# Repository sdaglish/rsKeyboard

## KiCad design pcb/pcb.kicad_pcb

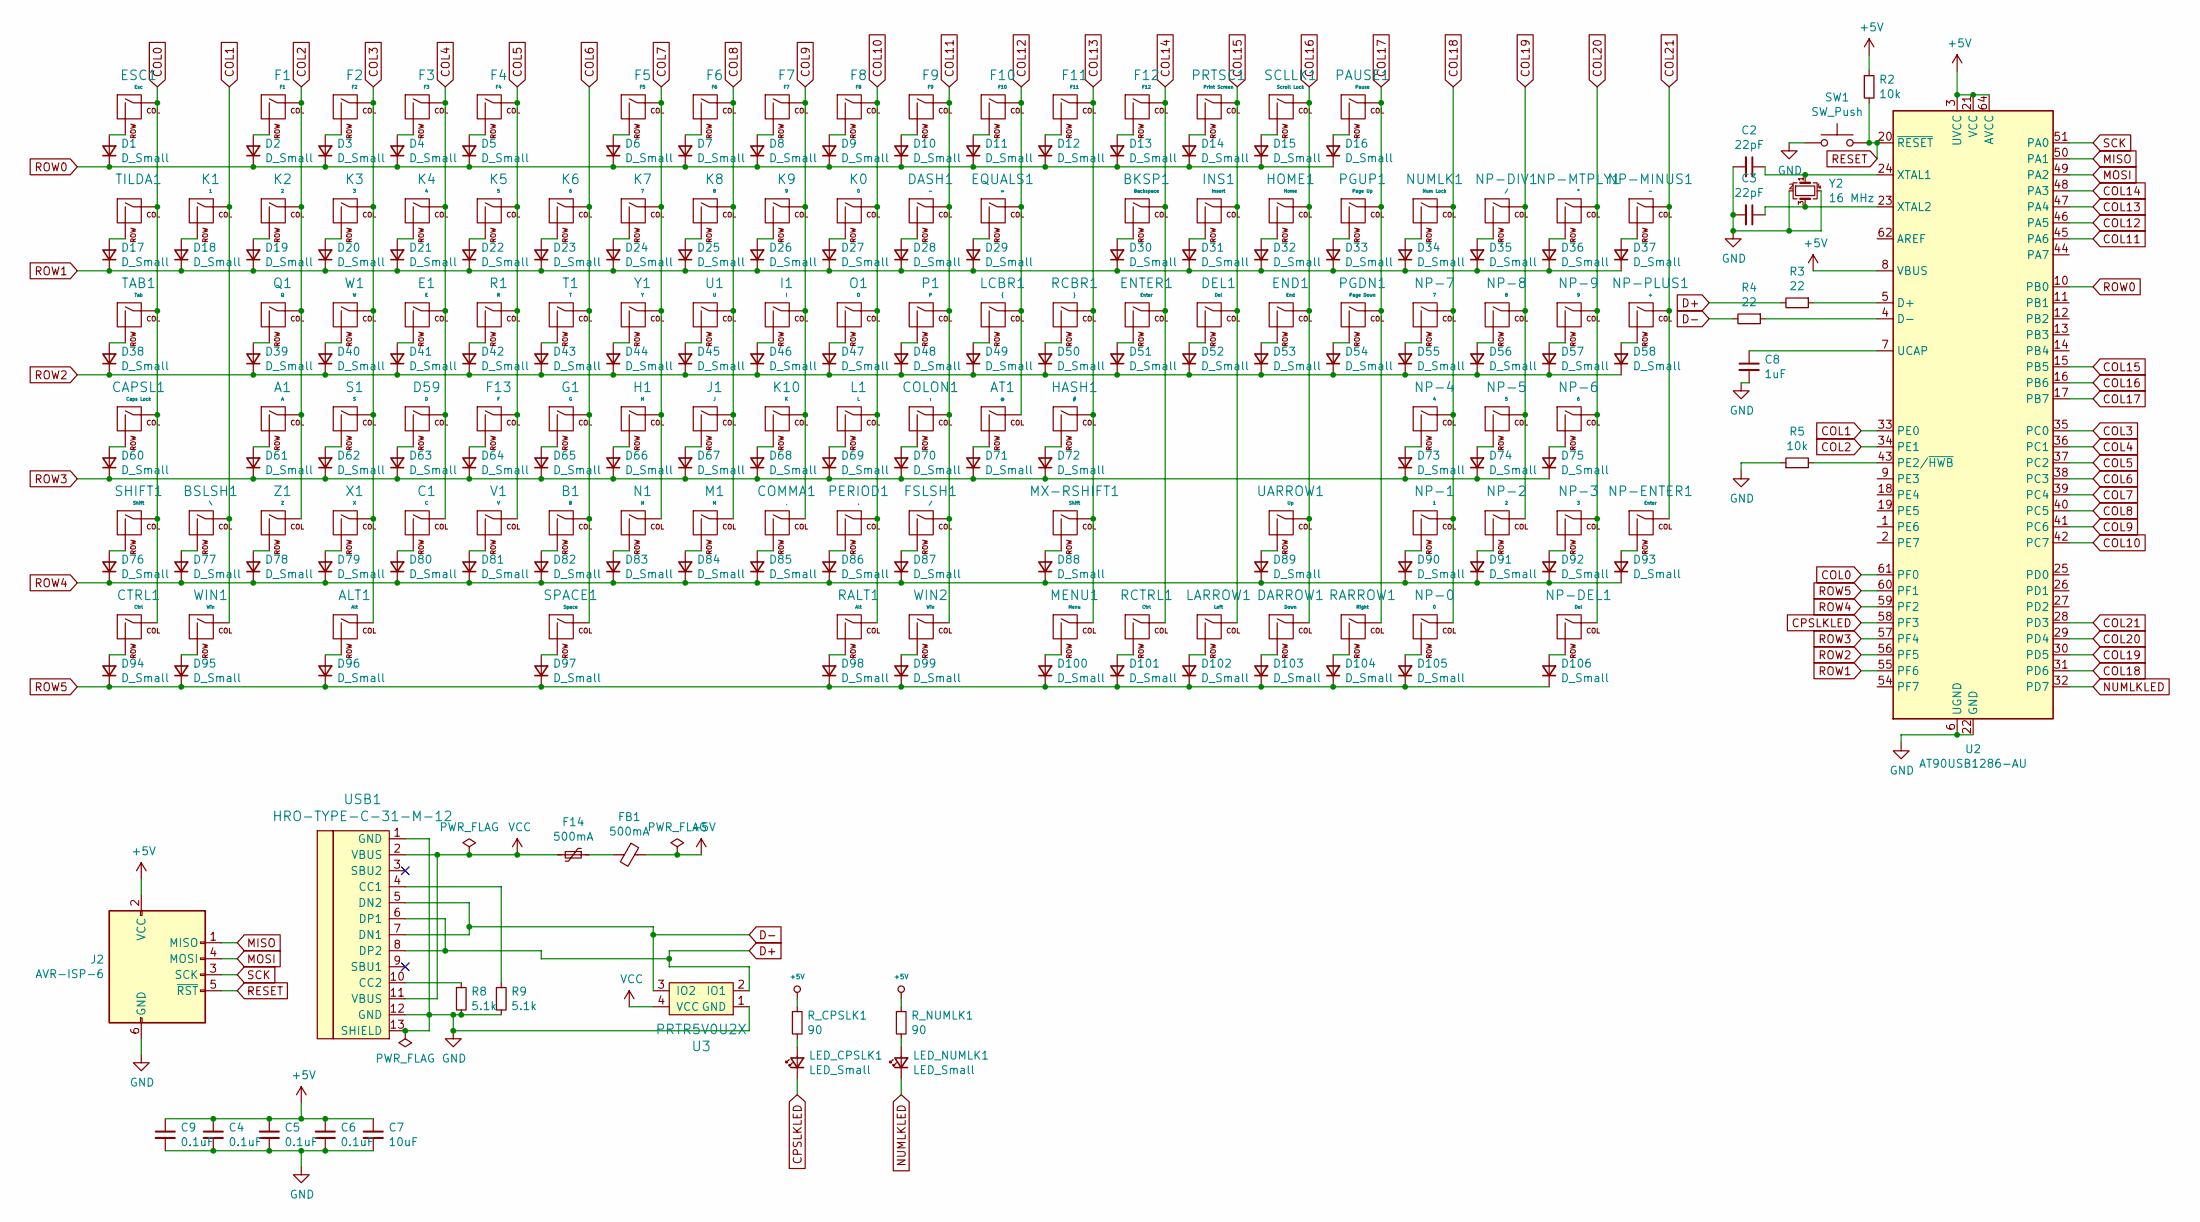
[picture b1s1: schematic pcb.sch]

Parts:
A1: A; MX-1U-NoLED
ALT1: Alt; MX-1U-NoLED
AT1: @; MX-1U-NoLED
B1: B; MX-1U-NoLED
BKSP1: Backspace; MX-2U-NoLED
BSLSH1: \\; MX-1U-NoLED
C1: C; MX-1U-NoLED
C2, C3: 22pF; C_0805_2012Metric
C4, C5, C6, C9: 0.1uF; C_0805_2012Metric
C7: 10uF; C_0805_2012Metric
C8: 1uF; C_0805_2012Metric
CAPSL1: Caps Lock; MX-1U-NoLED
COLON1: :; MX-1U-NoLED
COMMA1: ,; MX-1U-NoLED
CTRL1: Ctrl; MX-1U-NoLED
D1, D2, D3, D4, D5, D6, D7, D8, D9, D10, D11, D12, D13, D14, D15, D16, D17, D18, D19, D20, D21, D22, D23, D24, D25, D26, D27, D28, D29, D30, D31, D32, D33, D34, D35, D36, D37, D38, D39, D40, D41, D42, D43, D44, D45, D46, D47, D48, D49, D50, D51, D52, D53, D54, D55, D56, D57, D58, D60, D61, D62, D63, D64, D65, D66, D67, D68, D69, D70, D71, D72, D73, D74, D75, D76, D77, D78, D79, D80, D81, D82, D83, D84, D85, D86, D87, D88, D89, D90, D91, D92, D93, D94, D95, D96, D97, D98, D99, D100, D101, D102, D103, D104, D105, D106: D_Small; D_SOD-123
D59: D; MX-1U-NoLED
DARROW1: Down; MX-1U-NoLED
DASH1: -; MX-1U-NoLED
DEL1: Del; MX-1U-NoLED
E1: E; MX-1U-NoLED
END1: End; MX-1U-NoLED
ENTER1: Enter; MX-2U-NoLED
EQUALS1: =; MX-1U-NoLED
ESC1: Esc; MX-1U-NoLED
F1: F1; MX-1U-NoLED
F2: F2; MX-1U-NoLED
F3: F3; MX-1U-NoLED
F4: F4; MX-1U-NoLED
F5: F5; MX-1U-NoLED
F6: F6; MX-1U-NoLED
F7: F7; MX-1U-NoLED
F8: F8; MX-1U-NoLED
F9: F9; MX-1U-NoLED
F10: F10; MX-1U-NoLED
F11: F11; MX-1U-NoLED
F12: F12; MX-1U-NoLED
F13: F; MX-1U-NoLED
F14: 500mA; Fuse_0805_2012Metric
FB1: 500mA; R_0805_2012Metric
FSLSH1: /; MX-1U-NoLED
G1: G; MX-1U-NoLED
H1: H; MX-1U-NoLED
HASH1: #; MX-1U-NoLED
HOME1: Home; MX-1U-NoLED
I1: I; MX-1U-NoLED
INS1: Insert; MX-1U-NoLED
J1: J; MX-1U-NoLED
J2: AVR-ISP-6; Reset_Pretty-Mask
K0: 0; MX-1U-NoLED
K1: 1; MX-1U-NoLED
K2: 2; MX-1U-NoLED
K3: 3; MX-1U-NoLED
K4: 4; MX-1U-NoLED
K5: 5; MX-1U-NoLED
K6: 6; MX-1U-NoLED
K7: 7; MX-1U-NoLED
K8: 8; MX-1U-NoLED
K9: 9; MX-1U-NoLED
K10: K; MX-1U-NoLED
L1: L; MX-1U-NoLED
LARROW1: Left; MX-1U-NoLED
LCBR1: {; MX-1U-NoLED
LED_CPSLK1: LED_Small; LED_0805_2012Metric
LED_NUMLK1: LED_Small; LED_0805_2012Metric
M1: M; MX-1U-NoLED
MENU1: Menu; MX-1U-NoLED
MX-RSHIFT1: Shift; MX-2.75U-NoLED
N1: N; MX-1U-NoLED
NP-0: 0; MX-2U-NoLED
NP-1: 1; MX-1U-NoLED
NP-2: 2; MX-1U-NoLED
NP-3: 3; MX-1U-NoLED
NP-4: 4; MX-1U-NoLED
NP-5: 5; MX-1U-NoLED
NP-6: 6; MX-1U-NoLED
NP-7: 7; MX-1U-NoLED
NP-8: 8; MX-1U-NoLED
NP-9: 9; MX-1U-NoLED
NP-DEL1: Del; MX-1U-NoLED
NP-DIV1: /; MX-1U-NoLED
NP-ENTER1: Enter; MX-2U-NoLED
NP-MINUS1: -; MX-1U-NoLED
NP-MTPLY1: *; MX-1U-NoLED
NP-PLUS1: +; MX-2U-NoLED
NUMLK1: Num Lock; MX-1U-NoLED
O1: O; MX-1U-NoLED
P1: P; MX-1U-NoLED
PAUSE1: Pause; MX-1U-NoLED
PERIOD1: .; MX-1U-NoLED
PGDN1: Page Down; MX-1U-NoLED
PGUP1: Page Up; MX-1U-NoLED
PRTSC1: Print Screen; MX-1U-NoLED
Q1: Q; MX-1U-NoLED
R1: R; MX-1U-NoLED
R2, R5: 10k; R_0805_2012Metric
R3, R4: 22; R_0805_2012Metric
R8, R9: 5.1k; R_0805_2012Metric
RALT1: Alt; MX-1U-NoLED
RARROW1: Right; MX-1U-NoLED
RCBR1: }; MX-1U-NoLED
RCTRL1: Ctrl; MX-1U-NoLED
R_CPSLK1: 90; R_0805_2012Metric
R_NUMLK1: 90; R_0805_2012Metric
S1: S; MX-1U-NoLED
SCLLK1: Scroll Lock; MX-1U-NoLED
SHIFT1: Shift; MX-1U-NoLED
SPACE1: Space; MX-6.25U-NoLED
SW1: SW_Push; SKQG-1155865
T1: T; MX-1U-NoLED
TAB1: Tab; MX-1U-NoLED
TILDA1: MX-1U-NoLED
U1: U; MX-1U-NoLED
U2: AT90USB1286-AU; TQFP-64_14x14mm_P0.8mm
U3: PRTR5V0U2X; SOT143B
UARROW1: Up; MX-1U-NoLED
USB1: HRO-TYPE-C-31-M-12
V1: V; MX-1U-NoLED
W1: W; MX-1U-NoLED
WIN1, WIN2: Win; MX-1U-NoLED
X1: X; MX-1U-NoLED
Y1: Y; MX-1U-NoLED
Y2: 16 MHz; Crystal_SMD_3225-4Pin_3.2x2.5mm
Z1: Z; MX-1U-NoLED

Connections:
+5V: C4.1, C5.1, C6.1, C7.1, C9.1, FB1.1, J2.2 (VCC), R2.1, R_CPSLK1.1, R_NUMLK1.1, U2.3 (UVCC), U2.8 (VBUS), U2.21 (VCC), U2.52 (VCC), U2.64 (AVCC)
COL0: CAPSL1.1 (COL), CTRL1.1 (COL), ESC1.1 (COL), SHIFT1.1 (COL), TAB1.1 (COL), TILDA1.1 (COL), U2.61 (PF0)
COL1: BSLSH1.1 (COL), K1.1 (COL), U2.33 (PE0), WIN1.1 (COL)
COL2: A1.1 (COL), F1.1 (COL), K2.1 (COL), Q1.1 (COL), U2.34 (PE1), Z1.1 (COL)
COL3: ALT1.1 (COL), F2.1 (COL), K3.1 (COL), S1.1 (COL), U2.35 (PC0), W1.1 (COL), X1.1 (COL)
COL4: C1.1 (COL), D59.1 (COL), E1.1 (COL), F3.1 (COL), K4.1 (COL), U2.36 (PC1)
COL5: F4.1 (COL), F13.1 (COL), K5.1 (COL), R1.1 (COL), U2.37 (PC2), V1.1 (COL)
COL6: B1.1 (COL), G1.1 (COL), K6.1 (COL), SPACE1.1 (COL), T1.1 (COL), U2.38 (PC3)
COL7: F5.1 (COL), H1.1 (COL), K7.1 (COL), N1.1 (COL), U2.39 (PC4), Y1.1 (COL)
COL8: F6.1 (COL), J1.1 (COL), K8.1 (COL), M1.1 (COL), U1.1 (COL), U2.40 (PC5)
COL9: COMMA1.1 (COL), F7.1 (COL), I1.1 (COL), K9.1 (COL), K10.1 (COL), U2.41 (PC6)
COL10: F8.1 (COL), K0.1 (COL), L1.1 (COL), O1.1 (COL), PERIOD1.1 (COL), RALT1.1 (COL), U2.42 (PC7)
COL11: COLON1.1 (COL), DASH1.1 (COL), F9.1 (COL), FSLSH1.1 (COL), P1.1 (COL), U2.45 (PA6), WIN2.1 (COL)
COL12: AT1.1 (COL), EQUALS1.1 (COL), F10.1 (COL), LCBR1.1 (COL), U2.46 (PA5)
COL13: F11.1 (COL), HASH1.1 (COL), MENU1.1 (COL), MX-RSHIFT1.1 (COL), RCBR1.1 (COL), U2.47 (PA4)
COL14: BKSP1.1 (COL), ENTER1.1 (COL), F12.1 (COL), RCTRL1.1 (COL), U2.48 (PA3)
COL15: DEL1.1 (COL), INS1.1 (COL), LARROW1.1 (COL), PRTSC1.1 (COL), U2.15 (PB5)
COL16: DARROW1.1 (COL), END1.1 (COL), HOME1.1 (COL), SCLLK1.1 (COL), U2.16 (PB6), UARROW1.1 (COL)
COL17: PAUSE1.1 (COL), PGDN1.1 (COL), PGUP1.1 (COL), RARROW1.1 (COL), U2.17 (PB7)
COL18: NP-0.1 (COL), NP-1.1 (COL), NP-4.1 (COL), NP-7.1 (COL), NUMLK1.1 (COL), U2.31 (PD6)
COL19: NP-2.1 (COL), NP-5.1 (COL), NP-8.1 (COL), NP-DIV1.1 (COL), U2.30 (PD5)
COL20: NP-3.1 (COL), NP-6.1 (COL), NP-9.1 (COL), NP-DEL1.1 (COL), NP-MTPLY1.1 (COL), U2.29 (PD4)
COL21: NP-ENTER1.1 (COL), NP-MINUS1.1 (COL), NP-PLUS1.1 (COL), U2.28 (PD3)
CPSLKLED: LED_CPSLK1.1 (K), U2.58 (PF3)
D+: R3.2, U3.2 (IO1), USB1.6 (DP1), USB1.8 (DP2)
D-: R4.2, U3.3 (IO2), USB1.5 (DN2), USB1.7 (DN1)
GND: C2.2, C3.2, C4.2, C5.2, C6.2, C7.2, C8.2, C9.2, J2.6 (GND), R5.1, R8.2, R9.2, SW1.1, U2.6 (UGND), U2.22 (GND), U2.53 (GND), U2.63 (GND), U3.1 (GND), USB1.1 (GND), USB1.12 (GND), USB1.13 (SHIELD), Y2.2, Y2.4
MISO: J2.1 (MISO), U2.50 (PA1)
MOSI: J2.4 (MOSI), U2.49 (PA2)
NUMLKLED: LED_NUMLK1.1 (K), U2.32 (PD7)
unnamed: A1.2 (ROW), D61.2 (A)
unnamed: ALT1.2 (ROW), D96.2 (A)
unnamed: AT1.2 (ROW), D71.2 (A)
unnamed: B1.2 (ROW), D82.2 (A)
unnamed: BKSP1.2 (ROW), D30.2 (A)
unnamed: BSLSH1.2 (ROW), D77.2 (A)
unnamed: C1.2 (ROW), D80.2 (A)
unnamed: C2.1, U2.24 (XTAL1), Y2.1
unnamed: C3.1, U2.23 (XTAL2), Y2.3
unnamed: C8.1, U2.7 (UCAP)
unnamed: CAPSL1.2 (ROW), D60.2 (A)
unnamed: COLON1.2 (ROW), D70.2 (A)
unnamed: COMMA1.2 (ROW), D85.2 (A)
unnamed: CTRL1.2 (ROW), D94.2 (A)
unnamed: D1.2 (A), ESC1.2 (ROW)
unnamed: D2.2 (A), F1.2 (ROW)
unnamed: D3.2 (A), F2.2 (ROW)
unnamed: D4.2 (A), F3.2 (ROW)
unnamed: D5.2 (A), F4.2 (ROW)
unnamed: D6.2 (A), F5.2 (ROW)
unnamed: D7.2 (A), F6.2 (ROW)
unnamed: D8.2 (A), F7.2 (ROW)
unnamed: D9.2 (A), F8.2 (ROW)
unnamed: D10.2 (A), F9.2 (ROW)
unnamed: D11.2 (A), F10.2 (ROW)
unnamed: D12.2 (A), F11.2 (ROW)
unnamed: D13.2 (A), F12.2 (ROW)
unnamed: D14.2 (A), PRTSC1.2 (ROW)
unnamed: D15.2 (A), SCLLK1.2 (ROW)
unnamed: D16.2 (A), PAUSE1.2 (ROW)
unnamed: D17.2 (A), TILDA1.2 (ROW)
unnamed: D18.2 (A), K1.2 (ROW)
unnamed: D19.2 (A), K2.2 (ROW)
unnamed: D20.2 (A), K3.2 (ROW)
unnamed: D21.2 (A), K4.2 (ROW)
unnamed: D22.2 (A), K5.2 (ROW)
unnamed: D23.2 (A), K6.2 (ROW)
unnamed: D24.2 (A), K7.2 (ROW)
unnamed: D25.2 (A), K8.2 (ROW)
unnamed: D26.2 (A), K9.2 (ROW)
unnamed: D27.2 (A), K0.2 (ROW)
unnamed: D28.2 (A), DASH1.2 (ROW)
unnamed: D29.2 (A), EQUALS1.2 (ROW)
unnamed: D31.2 (A), INS1.2 (ROW)
unnamed: D32.2 (A), HOME1.2 (ROW)
unnamed: D33.2 (A), PGUP1.2 (ROW)
unnamed: D34.2 (A), NUMLK1.2 (ROW)
unnamed: D35.2 (A), NP-DIV1.2 (ROW)
unnamed: D36.2 (A), NP-MTPLY1.2 (ROW)
unnamed: D37.2 (A), NP-MINUS1.2 (ROW)
unnamed: D38.2 (A), TAB1.2 (ROW)
unnamed: D39.2 (A), Q1.2 (ROW)
unnamed: D40.2 (A), W1.2 (ROW)
unnamed: D41.2 (A), E1.2 (ROW)
unnamed: D42.2 (A), R1.2 (ROW)
unnamed: D43.2 (A), T1.2 (ROW)
unnamed: D44.2 (A), Y1.2 (ROW)
unnamed: D45.2 (A), U1.2 (ROW)
unnamed: D46.2 (A), I1.2 (ROW)
unnamed: D47.2 (A), O1.2 (ROW)
unnamed: D48.2 (A), P1.2 (ROW)
unnamed: D49.2 (A), LCBR1.2 (ROW)
unnamed: D50.2 (A), RCBR1.2 (ROW)
unnamed: D51.2 (A), ENTER1.2 (ROW)
unnamed: D52.2 (A), DEL1.2 (ROW)
unnamed: D53.2 (A), END1.2 (ROW)
unnamed: D54.2 (A), PGDN1.2 (ROW)
unnamed: D55.2 (A), NP-7.2 (ROW)
unnamed: D56.2 (A), NP-8.2 (ROW)
unnamed: D57.2 (A), NP-9.2 (ROW)
unnamed: D58.2 (A), NP-PLUS1.2 (ROW)
unnamed: D59.2 (ROW), D63.2 (A)
unnamed: D62.2 (A), S1.2 (ROW)
unnamed: D64.2 (A), F13.2 (ROW)
unnamed: D65.2 (A), G1.2 (ROW)
unnamed: D66.2 (A), H1.2 (ROW)
unnamed: D67.2 (A), J1.2 (ROW)
unnamed: D68.2 (A), K10.2 (ROW)
unnamed: D69.2 (A), L1.2 (ROW)
unnamed: D72.2 (A), HASH1.2 (ROW)
unnamed: D73.2 (A), NP-4.2 (ROW)
unnamed: D74.2 (A), NP-5.2 (ROW)
unnamed: D75.2 (A), NP-6.2 (ROW)
unnamed: D76.2 (A), SHIFT1.2 (ROW)
unnamed: D78.2 (A), Z1.2 (ROW)
unnamed: D79.2 (A), X1.2 (ROW)
unnamed: D81.2 (A), V1.2 (ROW)
unnamed: D83.2 (A), N1.2 (ROW)
unnamed: D84.2 (A), M1.2 (ROW)
unnamed: D86.2 (A), PERIOD1.2 (ROW)
unnamed: D87.2 (A), FSLSH1.2 (ROW)
unnamed: D88.2 (A), MX-RSHIFT1.2 (ROW)
unnamed: D89.2 (A), UARROW1.2 (ROW)
unnamed: D90.2 (A), NP-1.2 (ROW)
unnamed: D91.2 (A), NP-2.2 (ROW)
unnamed: D92.2 (A), NP-3.2 (ROW)
unnamed: D93.2 (A), NP-ENTER1.2 (ROW)
unnamed: D95.2 (A), WIN1.2 (ROW)
unnamed: D97.2 (A), SPACE1.2 (ROW)
unnamed: D98.2 (A), RALT1.2 (ROW)
unnamed: D99.2 (A), WIN2.2 (ROW)
unnamed: D100.2 (A), MENU1.2 (ROW)
unnamed: D101.2 (A), RCTRL1.2 (ROW)
unnamed: D102.2 (A), LARROW1.2 (ROW)
unnamed: D103.2 (A), DARROW1.2 (ROW)
unnamed: D104.2 (A), RARROW1.2 (ROW)
unnamed: D105.2 (A), NP-0.2 (ROW)
unnamed: D106.2 (A), NP-DEL1.2 (ROW)
unnamed: F14.1, FB1.2
unnamed: LED_CPSLK1.2 (A), R_CPSLK1.2
unnamed: LED_NUMLK1.2 (A), R_NUMLK1.2
unnamed: R3.1, U2.5 (D+)
unnamed: R4.1, U2.4 (D-)
unnamed: R5.2, U2.43 (PE2/~HWB)
unnamed: R8.1, USB1.10 (CC2)
unnamed: R9.1, USB1.4 (CC1)
RESET: J2.5 (~RST), R2.2, SW1.2, U2.20 (~RESET)
ROW0: D1.1 (K), D2.1 (K), D3.1 (K), D4.1 (K), D5.1 (K), D6.1 (K), D7.1 (K), D8.1 (K), D9.1 (K), D10.1 (K), D11.1 (K), D12.1 (K), D13.1 (K), D14.1 (K), D15.1 (K), D16.1 (K), U2.10 (PB0)
ROW1: D17.1 (K), D18.1 (K), D19.1 (K), D20.1 (K), D21.1 (K), D22.1 (K), D23.1 (K), D24.1 (K), D25.1 (K), D26.1 (K), D27.1 (K), D28.1 (K), D29.1 (K), D30.1 (K), D31.1 (K), D32.1 (K), D33.1 (K), D34.1 (K), D35.1 (K), D36.1 (K), D37.1 (K), U2.55 (PF6)
ROW2: D38.1 (K), D39.1 (K), D40.1 (K), D41.1 (K), D42.1 (K), D43.1 (K), D44.1 (K), D45.1 (K), D46.1 (K), D47.1 (K), D48.1 (K), D49.1 (K), D50.1 (K), D51.1 (K), D52.1 (K), D53.1 (K), D54.1 (K), D55.1 (K), D56.1 (K), D57.1 (K), D58.1 (K), U2.56 (PF5)
ROW3: D60.1 (K), D61.1 (K), D62.1 (K), D63.1 (K), D64.1 (K), D65.1 (K), D66.1 (K), D67.1 (K), D68.1 (K), D69.1 (K), D70.1 (K), D71.1 (K), D72.1 (K), D73.1 (K), D74.1 (K), D75.1 (K), U2.57 (PF4)
ROW4: D76.1 (K), D77.1 (K), D78.1 (K), D79.1 (K), D80.1 (K), D81.1 (K), D82.1 (K), D83.1 (K), D84.1 (K), D85.1 (K), D86.1 (K), D87.1 (K), D88.1 (K), D89.1 (K), D90.1 (K), D91.1 (K), D92.1 (K), D93.1 (K), U2.59 (PF2)
ROW5: D94.1 (K), D95.1 (K), D96.1 (K), D97.1 (K), D98.1 (K), D99.1 (K), D100.1 (K), D101.1 (K), D102.1 (K), D103.1 (K), D104.1 (K), D105.1 (K), D106.1 (K), U2.60 (PF1)
SCK: J2.3 (SCK), U2.51 (PA0)
VCC: F14.2, U3.4 (VCC), USB1.2 (VBUS), USB1.11 (VBUS)

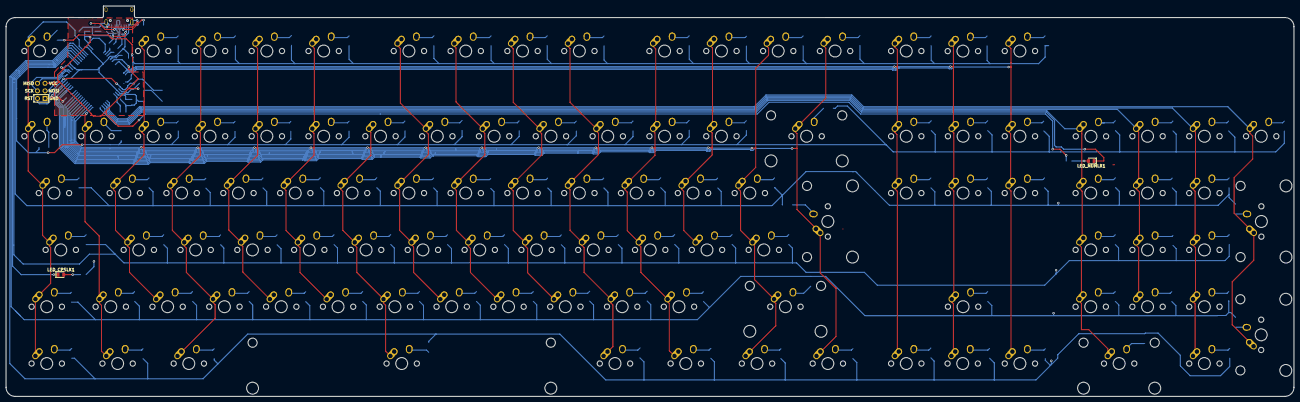
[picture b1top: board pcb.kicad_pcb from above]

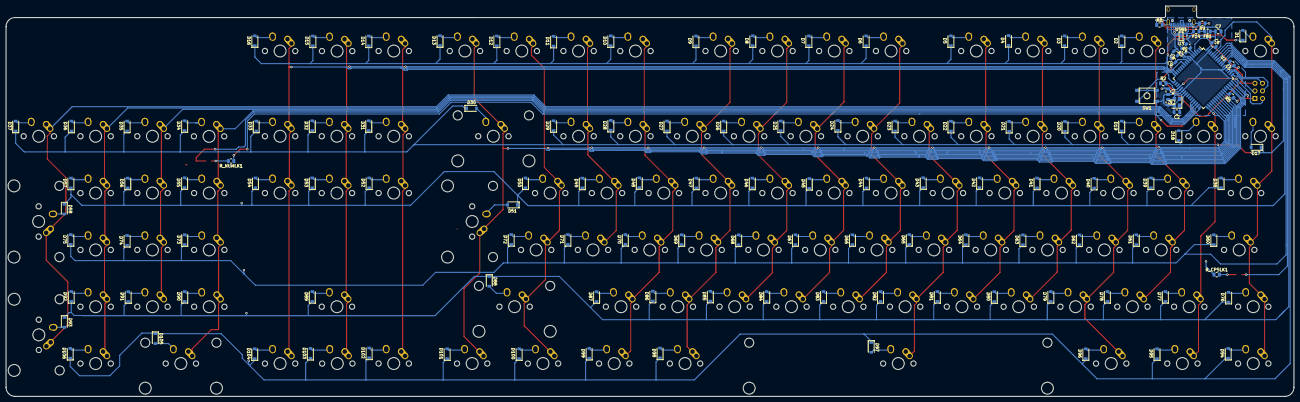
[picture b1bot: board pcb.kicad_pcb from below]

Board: 2 copper layers, 431.8 x 130.9 mm, 236 parts (128 on the bottom side), 155 nets.

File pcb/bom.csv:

"Id","Designator","Package","Quantity","Designation","Supplier and ref",
1,"USB1","Molex-0548190589",1,"Molex-0548190589",,,
2,"Y2","Crystal_SMD_3225-4Pin_3.2x2.5mm",1,"16 MHz",,,
3,"C6,C5,C4","C_0805_2012Metric",3,"0.1uF",,,
4,"Z1,Y1,X1,WIN2,WIN1,W1,V1,UARROW1,U1,TILDA1,TAB1,T1,SPACE1,SHIFT1,SCLLK1,S1,RCTRL1,RCBR1,RARROW1,RALT1,R1,Q1,PRTSC1,PGUP1,PGDN1,PERIOD1,PAUSE1,P1,O1,NUMLK1,NP-PLUS1,NP-MTPLY1,NP-MINUS1,NP-ENTER1,NP-DIV1,NP-DEL1,NP-9,NP-8,NP-7,NP-6,NP-5,NP-4,NP-3,NP-2,NP-1,NP-0,N1,MX-RSHIFT1,MENU1,M1,LCBR1,LARROW1,L1,K10,K9,K8,K7,K6,K5,K4,K3,K2,K1,K0,J1,INS1,I1,HOME1,HASH1,H1,G1,FSLSH1,F13,F12,F11,F10,F9,F8,F7,F6,F5,F4,F3,F2,F1,ESC1,EQUALS1,ENTER1,END1,E1,DEL1,DASH1,DARROW1,D59,CTRL1,COMMA1,COLON1,CAPSL1,C1,BSLSH1,BKSP1,B1,AT1,ALT1,A1","MX-1U-NoLED",105,"MX-NoLED",,,
5,"U2","TQFP-64_14x14mm_P0.8mm",1,"AT90USB1286-AU",,,
6,"SW1","SKQG-1155865",1,"SW_Push",,,
7,"R5,R2","R_0805_2012Metric",2,"10k",,,
8,"R4,R3","R_0805_2012Metric",2,"22",,,
9,"F14","Fuse_1206_3216Metric",1,"500mA",,,
10,"D106,D105,D104,D103,D102,D101,D100,D99,D98,D97,D96,D95,D94,D93,D92,D91,D90,D89,D88,D87,D86,D85,D84,D83,D82,D81,D80,D79,D78,D77,D76,D75,D74,D73,D72,D71,D70,D69,D68,D67,D66,D65,D64,D63,D62,D61,D60,D58,D57,D56,D55,D54,D53,D52,D51,D50,D49,D48,D47,D46,D45,D44,D43,D42,D41,D40,D39,D38,D37,D36,D35,D34,D33,D32,D31,D30,D29,D28,D27,D26,D25,D24,D23,D22,D21,D20,D19,D18,D17,D16,D15,D14,D13,D12,D11,D10,D9,D8,D7,D6,D5,D4,D3,D2,D1","D_SOD-123",105,"D_Small",,,
11,"C8","C_0805_2012Metric",1,"1uF",,,
12,"C7","C_0805_2012Metric",1,"10uF",,,
13,"C3,C2","C_0805_2012Metric",2,"22pF",,,

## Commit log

2021-06-25 deps: add submodules
2021-06-25 add keyboard-layout and cad files
2021-06-25 pcb: add base kicad project
2021-06-26 pcb: create pcb layout/design
2021-06-26 pcb: position switches on layout
2021-06-26 pcb: move diodes next to switches
2021-06-26 pcb: position components
2021-06-26 pcb: finish mcu positioning
2021-06-26 pcb: finish tracks on pcb
2021-06-26 pcb: reorganise, add bom+pos files
2021-06-26 pcb: reorganise schematic
2021-06-27 pcb: improve board design
2021-06-29 pcb: change to usb-c, reorganise pcb
2021-06-29 pcb: update helper files
2021-07-01 pcb: update edge cuts
